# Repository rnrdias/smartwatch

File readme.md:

# Smartwatch
É um relógio inteligente para micro controlador ATMEGA328P e display gráfico Nokia 5110.

#### Características:
- Data/Hora

- Alarme - Hora - Dia da semana

- Cronometro - Start,Stop e step

- Calendário

#### Motor gráfico:
- Lista

- Definir valor

- Definir valor sobre a lista

#### Estrutura de pastas do projeto
- electric: contem os esquemas elétrico e o layout
- docs: informações gerais e datasheets
- mechanic: projeto mecânico, posicionamento dos componentes
- firmware: contem o código fonte do smartwatch, compilação para AVR ou PC(simulador).

#### Detalhes do firmware:
+ app: aplicações executadas em segundo plano
+ build: binários gerados
+ kernel: núcleo do sistema
   + drivers: contem as interfaces e implementações dos hardwares
        + simulador: drivers para o simulador
        + atmega328p: drivers para o atmega328p
   + fonts: armazenamento de fontes
   + screen: telas do sistema
   + settings: definição das configurações e ligação das funções
   + upp: definição de funções para manipulação de gráficos baixo nível
+ language: definição dos idiomas
+ screens: telas para usuário final

#### Compilação:
Para o simulador:
```sh
$ make all_simulator
```
Para o avr:
```sh
$ make all_avr
```
Para recompilação (remove os arquivos binários e objetos):
```sh
$ make clean
```

#### Para o futuro:
+ integração com sistema Android, Bluetooth
    + sincronização das notificações
    + sincronização do calendário
    + identificação de ligações o número de telefone
+ controle de eletrodomésticos por infravermelho
+ contador de passos

### Licença
Copyright (c) 2015-2019 Ranieri Dias 
Todos os direitos reservados
Este arquivo é parte de Smartwatch.

O Smartwatch é um software livre: você pode redistribuí-lo e / ou modificar
sob os termos da Licença Pública Geral GNU, publicada pela
Free Software Foundation, versão 3 da Licença ou
(a seu critério) qualquer versão posterior.
O Smartwatch é distribuído na esperança de que seja útil,
mas SEM QUALQUER GARANTIA; sem sequer a garantia implícita de
COMERCIALIZAÇÃO ou ADEQUAÇÃO PARA UMA FINALIDADE ESPECÍFICA. Veja o
GNU General Public License para mais detalhes.
Você deveria ter recebido uma cópia da Licença Pública Geral GNU
junto com o Smartwatch. Caso contrário, consulte http://www.gnu.org/licenses/.

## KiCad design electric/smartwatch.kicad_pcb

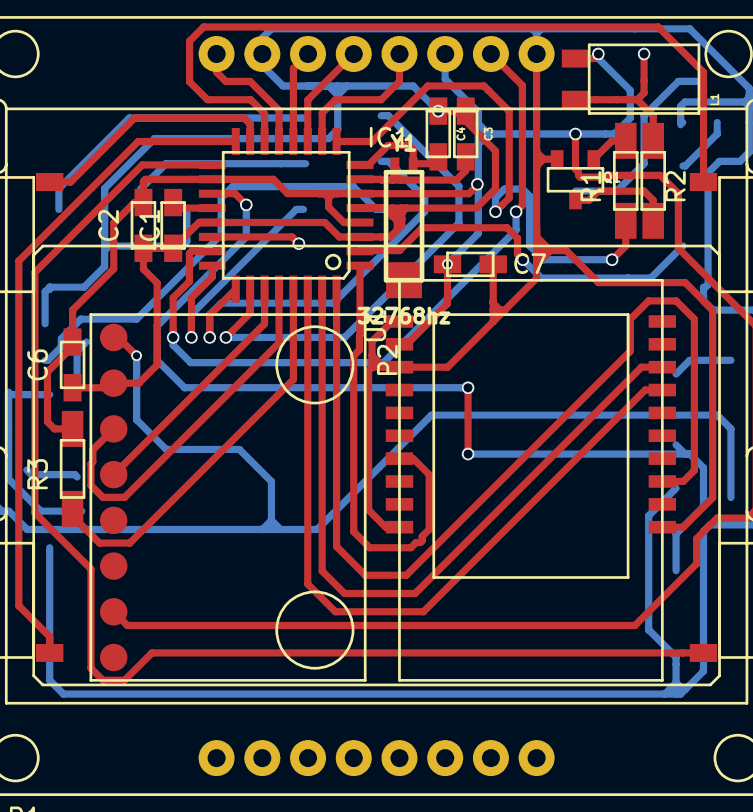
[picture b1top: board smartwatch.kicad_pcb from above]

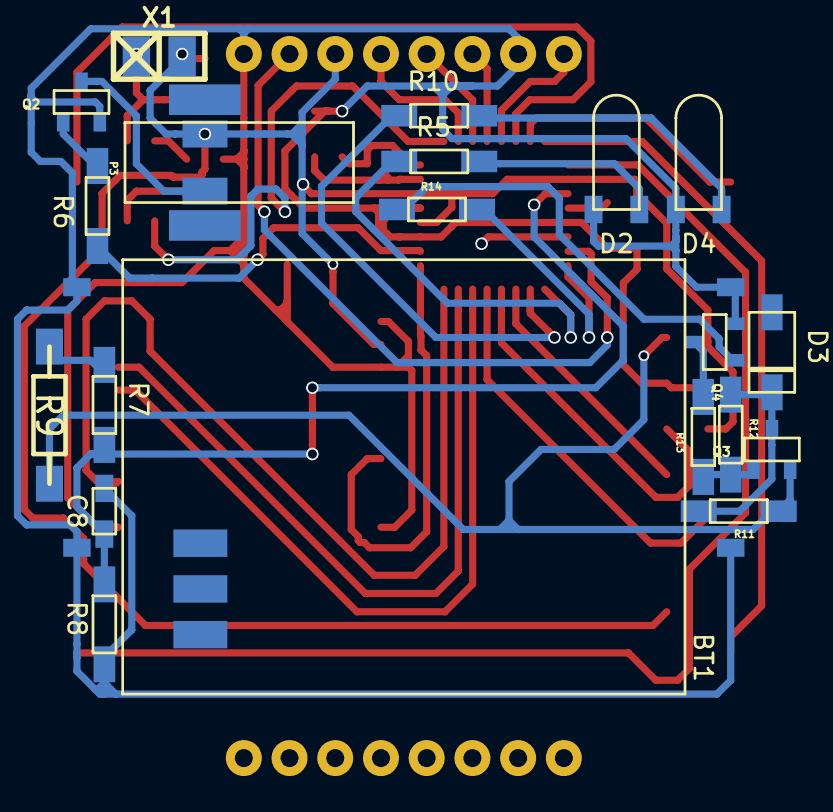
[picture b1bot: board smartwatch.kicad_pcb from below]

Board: 2 copper layers, 40 parts (20 on the bottom side), 40 nets.

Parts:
BT1: 3,8V/380mA; Bat_3.8V
C1: 10nF; Cap_SMD
C2, C6, C7, C8: 100nF; Cap_SMD
C3, C4: 6pF; Cap_SMD
D2: LED_POWER; LED_H
D3: D; D_SMD
D4: LED_IR; LED_H
IC1: ATMEGA328P-A; 32A
L1: 15mH; Indutor_15mH
P1: NOKIA_5110; LCD_nokia5110
P2: MPU6050
P3: VIRBRATOR; Vibr
Q1, Q2, Q4: BC337; SOT23
Q3: BC237; SOT23
R1, R6, R13, R14: 470R; R_SMD
R2, R5, R10: 100R; R_SMD
R3: 10K; R_SMD
R7: 300K; R_SMD
R8: 100K; R_SMD
R9: 10R/0,5W; RC03_SMD
R11: 270R; R_SMD
R12: 1K; R_SMD
SW1, SW2: SW_PUSH; Button_Horizontal_pin_mirror
SW3, SW4: SW_PUSH; Button_Horizontal
U1: E104-BT02
X1: Buzz; pin_socket_2_smd
Y1: 32768hz; crystal_tc-26_horiz

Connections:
+BATT: P2.1, Q3.2, R9.2, R11.2
ACC_SCL: IC1.28, P2.3
ACC_SDA: IC1.27, P2.4
BAT_RECARGA: IC1.24, R14.1
BAT_VOLT: C8.1, IC1.19, R7.1, R8.2
BLUE_D/C: IC1.32, U1.3
BLUE_RX: IC1.31, U1.8
BLUE_S/~M: IC1.1, U1.17
BLUE_TX: IC1.30, U1.7
BUT_A: IC1.14, SW1.1
BUT_B: IC1.15, SW4.1
BUT_C: IC1.16, SW2.1
BUT_D: IC1.17, SW3.1
BUZ: IC1.9, R1.2
CLOCK_1A: C3.1, IC1.7, Y1.1
CLOCK_1B: C4.1, IC1.8, Y1.2
FIRM_UPDADE_RESET: IC1.29, R3.2
IR_LED: IC1.26, R10.2
LCD_D/~C: IC1.12, P1.3
LCD_LAMP: IC1.23, P1.7
LCD_REST: IC1.13, P1.1
LCD_SCE: BT1.2, C1.2, C2.2, C3.2, C4.2, C6.2, C7.2, C8.2, D2.1, D4.1, IC1.3, IC1.5, IC1.21, P1.2, P1.8, P2.2, Q1.2, Q2.2, Q4.2, R8.1, SW1.2, SW2.2, SW3.2, SW4.2, U1.1, U1.11, U1.13, U1.20
LCD_SCLK: IC1.10, P1.5
LCD_SDIN: IC1.11, P1.4
unnamed: BT1.1, R7.2, R9.1
unnamed: C1.1, IC1.20
unnamed: D2.2, R5.1
unnamed: D3.1, Q3.3, R11.1, R12.2
unnamed: D4.2, R10.1
unnamed: L1.1, R2.1, X1.1
unnamed: P3.2, Q2.3
unnamed: Q1.1, R1.1
unnamed: Q1.3, R2.2
unnamed: Q2.1, R6.1
unnamed: Q3.1, R12.1, R13.2
unnamed: Q4.1, R14.2
unnamed: Q4.3, R13.1
POWER_LED: IC1.25, R5.2
VCC: C2.1, C6.1, C7.1, IC1.4, IC1.6, IC1.18, L1.2, P1.6, P2.7, P3.1, R3.1, U1.12, X1.2
VIBRA: IC1.2, R6.2

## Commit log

2018-05-09 estrutura inicial
2018-05-10 telas preparo
2018-05-13 lang adicionado
2018-05-13 parcial RTC
2018-05-15 telas estrutura
2018-05-15 tela main dia da semana Ok
2018-05-16 bip driver ok
2018-05-27 alarmes setting parcial
2018-05-29 alarmes settings ok
2018-05-29 adição de onResume onPause nos screens (redução da alocação de memoria)
2018-05-29 correção telas alarms e remoção file mem
2018-05-31 calendar edit ok
2018-05-31 sleep ok
2018-06-01 barra status parcial
2018-06-01 remocao de arquivo nao necessario
2018-06-01 mudança para suporte const _ parcial
2018-06-03 const tela status
2018-06-03 const para demais telas
2018-06-06 const app
2018-06-26 mudanca para o linux
2018-07-08 stopwatch parcial
2018-07-10 funcoes de controle EventHandler
2018-07-10 stopwatch ok
2018-07-11 nova estrutura para memoria
2018-07-11 organizacao do codigo
2018-07-14 reorganização da estrutura de diretorios
2018-07-15 sincronizacao ok
2018-07-15 alteracao para a sincronizacao do arquivo
2018-07-15 smartwatch funcao pause piscadas
2018-07-15 screen bug de memoria correcao, alocacao dinamica de memoria
2018-07-16 Status bar Ok
2018-07-16 main info
2018-07-17 ajustes finos nos screens
2018-07-17 Gerenciamento de energia
2018-07-19 bipe ok
2018-07-20 bipe ajustes
2019-08-19 Alterações para execução sem problemas
2019-10-08 restruturacao do projeto
2019-10-08 configurações ok
2019-11-22 restructuring of archives
2019-11-23 add m328p support
2019-11-24 make clean - interrupt simulator
2019-11-26 add files mechanic, docs and electric
2019-12-02 license files
2019-12-07 add images readme.md
2019-12-07 correcting images readme.md (base64 no work)
